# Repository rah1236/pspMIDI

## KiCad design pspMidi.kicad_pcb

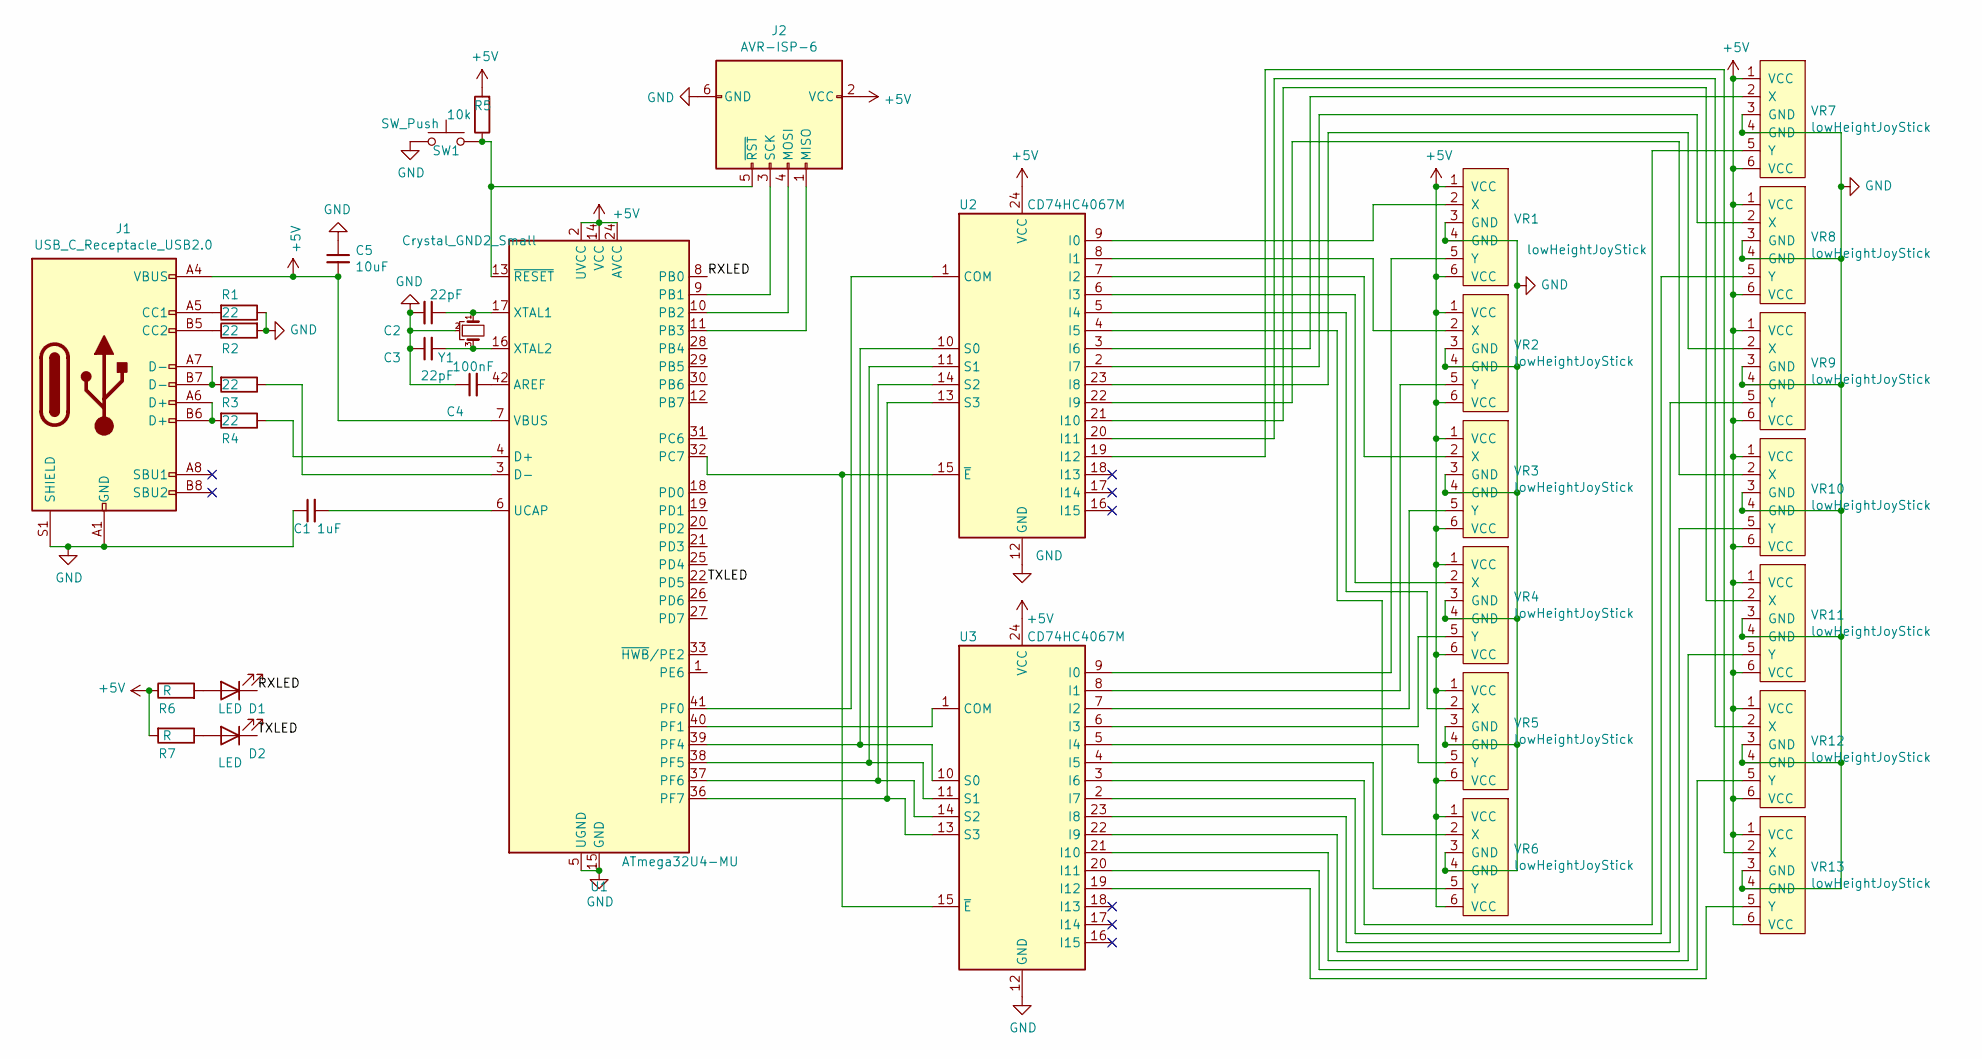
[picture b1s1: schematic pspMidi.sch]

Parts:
C1: 1uF; C_0603_1608Metric_Pad1.08x0.95mm_HandSolder
C2, C3: 22pF; C_0603_1608Metric_Pad1.08x0.95mm_HandSolder
C4: 100nF; C_0603_1608Metric_Pad1.08x0.95mm_HandSolder
C5: 10uF; C_0603_1608Metric_Pad1.08x0.95mm_HandSolder
D1, D2: LED; LED_0603_1608Metric_Castellated
J1: USB_C_Receptacle_USB2.0; USB_C_Receptacle_GCT_USB4085
J2: AVR-ISP-6; PinHeader_2x03_P2.54mm_Vertical
R1, R2, R3, R4: 22; R_0603_1608Metric_Pad0.98x0.95mm_HandSolder
R5: 10k; R_0603_1608Metric_Pad0.98x0.95mm_HandSolder
R6, R7: R; R_0603_1608Metric_Pad0.98x0.95mm_HandSolder
SW1: SW_Push; SW_PUSH_6mm
U1: ATmega32U4-MU; QFN-44-1EP_7x7mm_P0.5mm_EP5.2x5.2mm
U2, U3: CD74HC4067M; SOIC-24W_7.5x15.4mm_P1.27mm
VR1, VR2, VR3, VR4, VR5, VR6, VR7, VR8, VR9, VR10, VR11, VR12, VR13: lowHeightJoyStick; LowHeightJoyStick
Y1: Crystal_GND2_Small; Crystal_SMD_3225-4Pin_3.2x2.5mm_HandSoldering

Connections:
+5V: C5.2, J1.A4 (VBUS), J1.A9 (VBUS), J1.B4 (VBUS), J1.B9 (VBUS), J2.2 (VCC), R5.2, R6.1, R7.2, U1.2 (UVCC), U1.7 (VBUS), U1.14 (VCC), U1.24 (AVCC), U1.34 (VCC), U1.44 (AVCC), U2.24 (VCC), U3.24 (VCC), VR1.1 (VCC), VR1.6 (VCC), VR2.1 (VCC), VR2.6 (VCC), VR3.1 (VCC), VR3.6 (VCC), VR4.1 (VCC), VR4.6 (VCC), VR5.1 (VCC), VR5.6 (VCC), VR6.1 (VCC), VR6.6 (VCC), VR7.1 (VCC), VR7.6 (VCC), VR8.1 (VCC), VR8.6 (VCC), VR9.1 (VCC), VR9.6 (VCC), VR10.1 (VCC), VR10.6 (VCC), VR11.1 (VCC), VR11.6 (VCC), VR12.1 (VCC), VR12.6 (VCC), VR13.1 (VCC), VR13.6 (VCC)
/RXLED: D1.1 (K), U1.8 (PB0)
/TXLED: D2.1 (K), U1.22 (PD5)
GND: C1.1, C2.2, C3.1, C4.1, C5.1, J1.A1 (GND), J1.A12 (GND), J1.B1 (GND), J1.B12 (GND), J1.S1 (SHIELD), J2.6 (GND), R1.1, R2.2, SW1.1, U1.5 (UGND), U1.15 (GND), U1.23 (GND), U1.35 (GND), U1.43 (GND), U1.45 (GND), U2.12 (GND), U3.12 (GND), VR1.3 (GND), VR1.4 (GND), VR2.3 (GND), VR2.4 (GND), VR3.3 (GND), VR3.4 (GND), VR4.3 (GND), VR4.4 (GND), VR5.3 (GND), VR5.4 (GND), VR6.3 (GND), VR6.4 (GND), VR7.3 (GND), VR7.4 (GND), VR8.3 (GND), VR8.4 (GND), VR9.3 (GND), VR9.4 (GND), VR10.3 (GND), VR10.4 (GND), VR11.3 (GND), VR11.4 (GND), VR12.3 (GND), VR12.4 (GND), VR13.3 (GND), VR13.4 (GND), Y1.2
unnamed: C1.2, U1.6 (UCAP)
unnamed: C2.1, U1.17 (XTAL1), Y1.1
unnamed: C3.2, U1.16 (XTAL2), Y1.3
unnamed: C4.2, U1.42 (AREF)
unnamed: D1.2 (A), R6.2
unnamed: D2.2 (A), R7.1
unnamed: J1.A5 (CC1), R1.2
unnamed: J1.A6 (D+), J1.B6 (D+), R4.2
unnamed: J1.A7 (D-), J1.B7 (D-), R3.2
unnamed: J1.B5 (CC2), R2.1
unnamed: J2.1 (MISO), U1.11 (PB3)
unnamed: J2.3 (SCK), U1.9 (PB1)
unnamed: J2.4 (MOSI), U1.10 (PB2)
unnamed: J2.5 (~RST), R5.1, SW1.2, U1.13 (~RESET)
unnamed: R3.1, U1.3 (D-)
unnamed: R4.1, U1.4 (D+)
unnamed: U1.32 (PC7), U2.15 (~E), U3.15 (~E)
unnamed: U1.36 (PF7), U2.13 (S3), U3.13 (S3)
unnamed: U1.37 (PF6), U2.14 (S2), U3.14 (S2)
unnamed: U1.38 (PF5), U2.11 (S1), U3.11 (S1)
unnamed: U1.39 (PF4), U2.10 (S0), U3.10 (S0)
unnamed: U1.40 (PF1), U3.1 (COM)
unnamed: U1.41 (PF0), U2.1 (COM)
unnamed: U2.2 (I7), VR8.2 (X)
unnamed: U2.3 (I6), VR7.2 (X)
unnamed: U2.4 (I5), VR6.2 (X)
unnamed: U2.5 (I4), VR5.2 (X)
unnamed: U2.6 (I3), VR4.2 (X)
unnamed: U2.7 (I2), VR3.2 (X)
unnamed: U2.8 (I1), VR2.2 (X)
unnamed: U2.9 (I0), VR1.2 (X)
unnamed: U2.19 (I12), VR13.2 (X)
unnamed: U2.20 (I11), VR12.2 (X)
unnamed: U2.21 (I10), VR11.2 (X)
unnamed: U2.22 (I9), VR10.2 (X)
unnamed: U2.23 (I8), VR9.2 (X)
unnamed: U3.2 (I7), VR8.5 (Y)
unnamed: U3.3 (I6), VR7.5 (Y)
unnamed: U3.4 (I5), VR6.5 (Y)
unnamed: U3.5 (I4), VR5.5 (Y)
unnamed: U3.6 (I3), VR4.5 (Y)
unnamed: U3.7 (I2), VR3.5 (Y)
unnamed: U3.8 (I1), VR2.5 (Y)
unnamed: U3.9 (I0), VR1.5 (Y)
unnamed: U3.19 (I12), VR13.5 (Y)
unnamed: U3.20 (I11), VR12.5 (Y)
unnamed: U3.21 (I10), VR11.5 (Y)
unnamed: U3.22 (I9), VR10.5 (Y)
unnamed: U3.23 (I8), VR9.5 (Y)

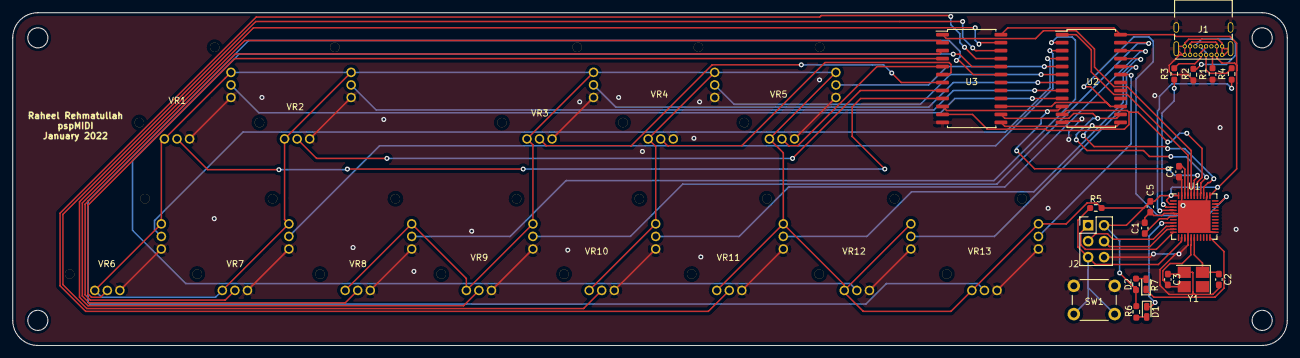
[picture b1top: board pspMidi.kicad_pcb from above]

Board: 2 copper layers, 203.0 x 53.0 mm, 34 parts (0 on the bottom side), 53 nets.

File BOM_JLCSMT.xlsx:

Comment | Designator | Footprint | JLCPCB Part #（optional）
MUX | U2,U3 | SOIC-24_7.5x15.4x1.27P | C496123
ATMEGA32U4-MU | U1 | VQFN-44_EP_7.0x7.0x0.5P | C112161
0603WAF220JT5E (22OHM) | R1,R2,R3,R4 | 0603 | C23345
0603WAF1002T5E (10kOHM | R5 | 0603 | C25804
1uF | C1 | 0603 | C15849
22pF | C2,C3 | 0603 | C1653
100nF | C4 | 0603 | C14663
10uF | C5 | 0603 | C96446
Blue LEDS | D1,D2 | 0603 | C375446
73.2 OHM LED Resistors | R6,R7 | 0603 | C23105
Crystal 16mhz | Y1 | 3.2x2.5 mm | C13738

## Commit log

2022-01-25 V1 done
